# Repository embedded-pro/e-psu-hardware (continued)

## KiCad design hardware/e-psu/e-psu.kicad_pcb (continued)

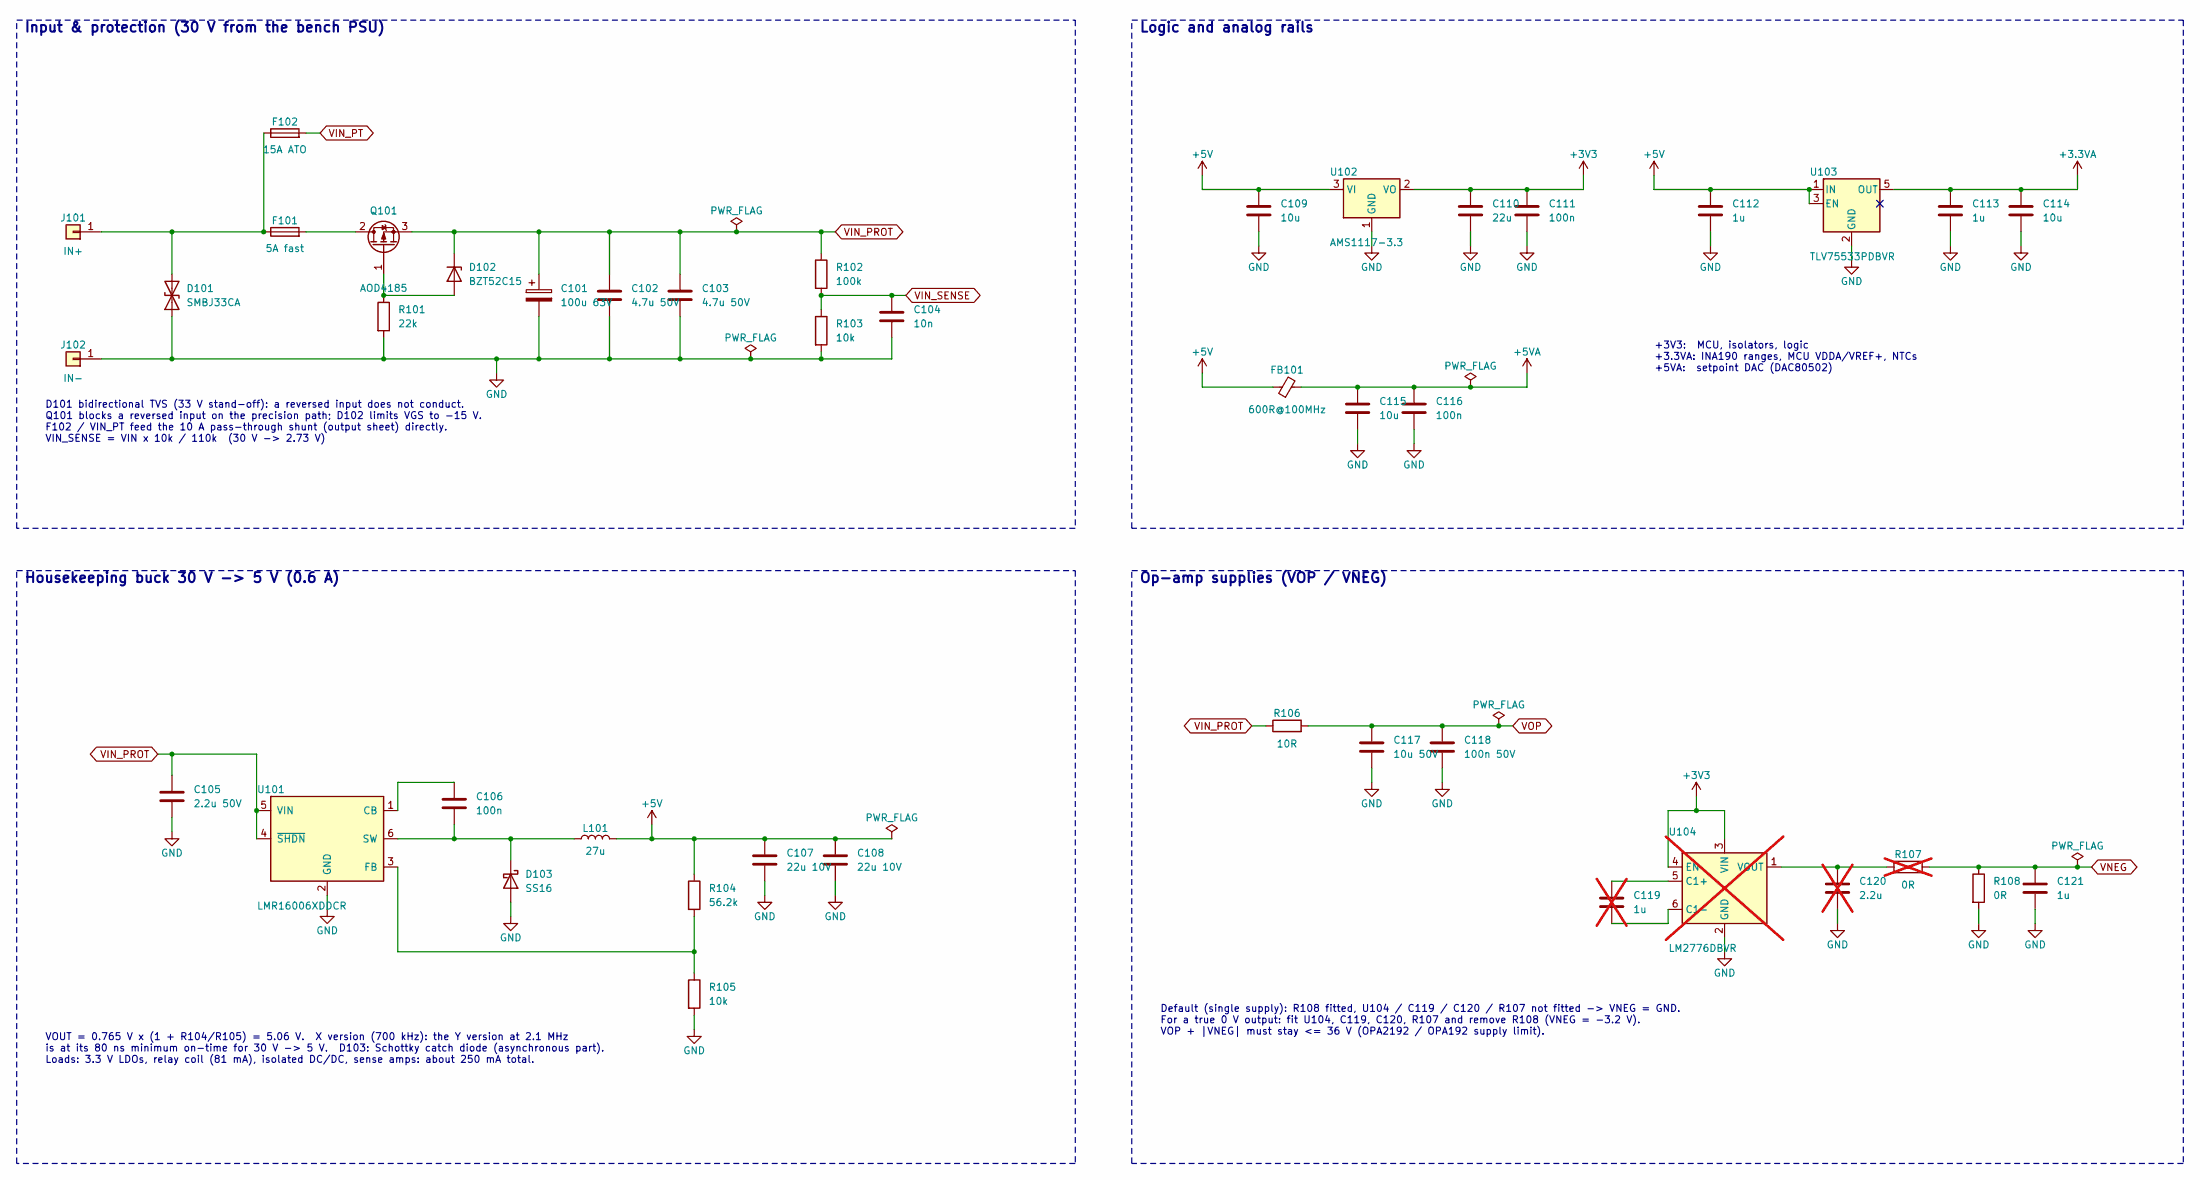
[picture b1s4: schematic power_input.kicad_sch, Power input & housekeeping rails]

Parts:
C101: 100u 63V; CP_Elec_10x10.5
C102, C103: 4.7u 50V; C_1210_3225Metric
C104: 10n; C_0603_1608Metric
C105: 2.2u 50V; C_1206_3216Metric
C106, C111, C116: 100n; C_0603_1608Metric
C107, C108: 22u 10V; C_0805_2012Metric
C109, C114, C115: 10u; C_0805_2012Metric
C110: 22u; C_1206_3216Metric
C112, C113, C121: 1u; C_0603_1608Metric
C117: 10u 50V; C_1210_3225Metric
C118: 100n 50V; C_0603_1608Metric
C119: 1u; C_0603_1608Metric; not fitted
C120: 2.2u; C_0603_1608Metric; not fitted
D101: SMBJ33CA; D_SMB; MPN SMBJ33CA (bidirectional)
D102: BZT52C15; D_SOD-123
D103: SS16; D_SMA
F101: 5A fast; Fuse_Littelfuse-NANO2-451_453; MPN Littelfuse 0451005.MRL (NANO2 5 A)
F102: 15A ATO; FuseHolder_Blade_ATO_Littelfuse_FLR_178.6165; MPN ATO blade fuse 15 A + PCB holder
FB101: 600R@100MHz; L_0805_2012Metric
J101: IN+; Banana_Cliff_FCR7350R_S16N-PC_Horizontal; MPN Cliff FCR7350R (4 mm, 16 A)
J102: IN-; Banana_Cliff_FCR7350B_S16N-PC_Horizontal; MPN Cliff FCR7350B (4 mm, 16 A)
L101: 27u; L_Sunlord_SWPA5040S; MPN 27 uH, Isat >= 1 A (e.g. Sunlord SWPA50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
Q101: AOD4185; TO-252-2; MPN AOD4185 (-40 V, 40 A, DPAK)
R101: 22k; R_0603_1608Metric
R102: 100k; R_0603_1608Metric
R103, R105: 10k; R_0603_1608Metric
R104: 56.2k; R_0603_1608Metric
R106: 10R; R_0805_2012Metric
R107: 0R; R_0603_1608Metric; not fitted
R108: 0R; R_0603_1608Metric
U101: LMR16006XDDCR; SOT-23-6; MPN TI LMR16006XDDCR (700 kHz)
U102: AMS1117-3.3; SOT-223-3_TabPin2; LCSC C6186
U103: TLV75533PDBVR; SOT-23-5; LCSC C404027
U104: LM2776DBVR; SOT-23-6; LCSC C69527; not fitted

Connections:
+3.3VA: C113.1, C114.1, U103.5 (OUT); also elsewhere on the board
+3V3: C110.1, C111.1, U102.2 (VO), U104.3 (VIN), U104.4 (EN); also elsewhere on the board
+5V: C107.1, C108.1, C109.1, C112.1, FB101.1, L101.2, R104.1, U102.3 (VI), U103.1 (IN), U103.3 (EN); also elsewhere on the board
+5VA: C115.1, C116.1, FB101.2; also elsewhere on the board
GND: C101.2, C102.2, C103.2, C104.2, C105.2, C107.2, C108.2, C109.2, C110.2, C111.2, C112.2, C113.2, C114.2, C115.2, C116.2, C117.2, C118.2, C120.2, C121.2, D101.1 (A1), D103.2 (A), J102.1, R101.2, R103.2, R105.2, R108.2, U101.2 (GND), U102.1 (GND), U103.2 (GND), U104.2 (GND); also elsewhere on the board
unnamed: D101.2 (A2), F101.1, F102.1, J101.1
unnamed: D102.2 (A), Q101.1 (G), R101.1
unnamed: C106.2, D103.1 (K), L101.1, U101.6 (SW)
unnamed: F101.2, Q101.2 (D)
unnamed: C106.1, U101.1 (CB)
unnamed: R104.2, R105.1, U101.3 (FB)
unnamed: C119.1, U104.5 (C1+)
unnamed: C119.2, U104.6 (C1-)
unnamed: C120.1, R107.1, U104.1 (VOUT)
VIN_PROT: C101.1, C102.1, C103.1, C105.1, D102.1 (K), Q101.3 (S), R102.1, R106.1, U101.4 (~SHDN), U101.5 (VIN); also elsewhere on the board
VIN_PT: F102.2; also elsewhere on the board
VIN_SENSE: C104.1, R102.2, R103.1; also elsewhere on the board
VNEG: C121.1, R107.2, R108.1; also elsewhere on the board
VOP: C117.1, C118.1, R106.2; also elsewhere on the board

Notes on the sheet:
Input & protection (30 V from the bench PSU)
D101 bidirectional TVS (33 V stand-off): a reversed input does not conduct. Q101 blocks a reversed input on the precision path; D102 limits VGS to -15 V. F102 / VIN_PT feed the 10 A pass-through shunt (output sheet) directly. VIN_SENSE = VIN x 10k / 110k (30 V -> 2.73 V)
Housekeeping buck 30 V -> 5 V (0.6 A)
VOUT = 0.765 V x (1 + R104/R105) = 5.06 V. X version (700 kHz): the Y version at 2.1 MHz is at its 80 ns minimum on-time for 30 V -> 5 V. D103: Schottky catch diode (asynchronous part). Loads: 3.3 V LDOs, relay coil (81 mA), isolated DC/DC, sense amps: about 250 mA total.
Logic and analog rails
+3V3: MCU, isolators, logic +3.3VA: INA190 ranges, MCU VDDA/VREF+, NTCs +5VA: setpoint DAC (DAC80502)
Op-amp supplies (VOP / VNEG)
Default (single supply): R108 fitted, U104 / C119 / C120 / R107 not fitted -> VNEG = GND. For a true 0 V output: fit U104, C119, C120, R107 and remove R108 (VNEG = -3.2 V). VOP + |VNEG| must stay <= 36 V (OPA2192 / OPA192 supply limit).

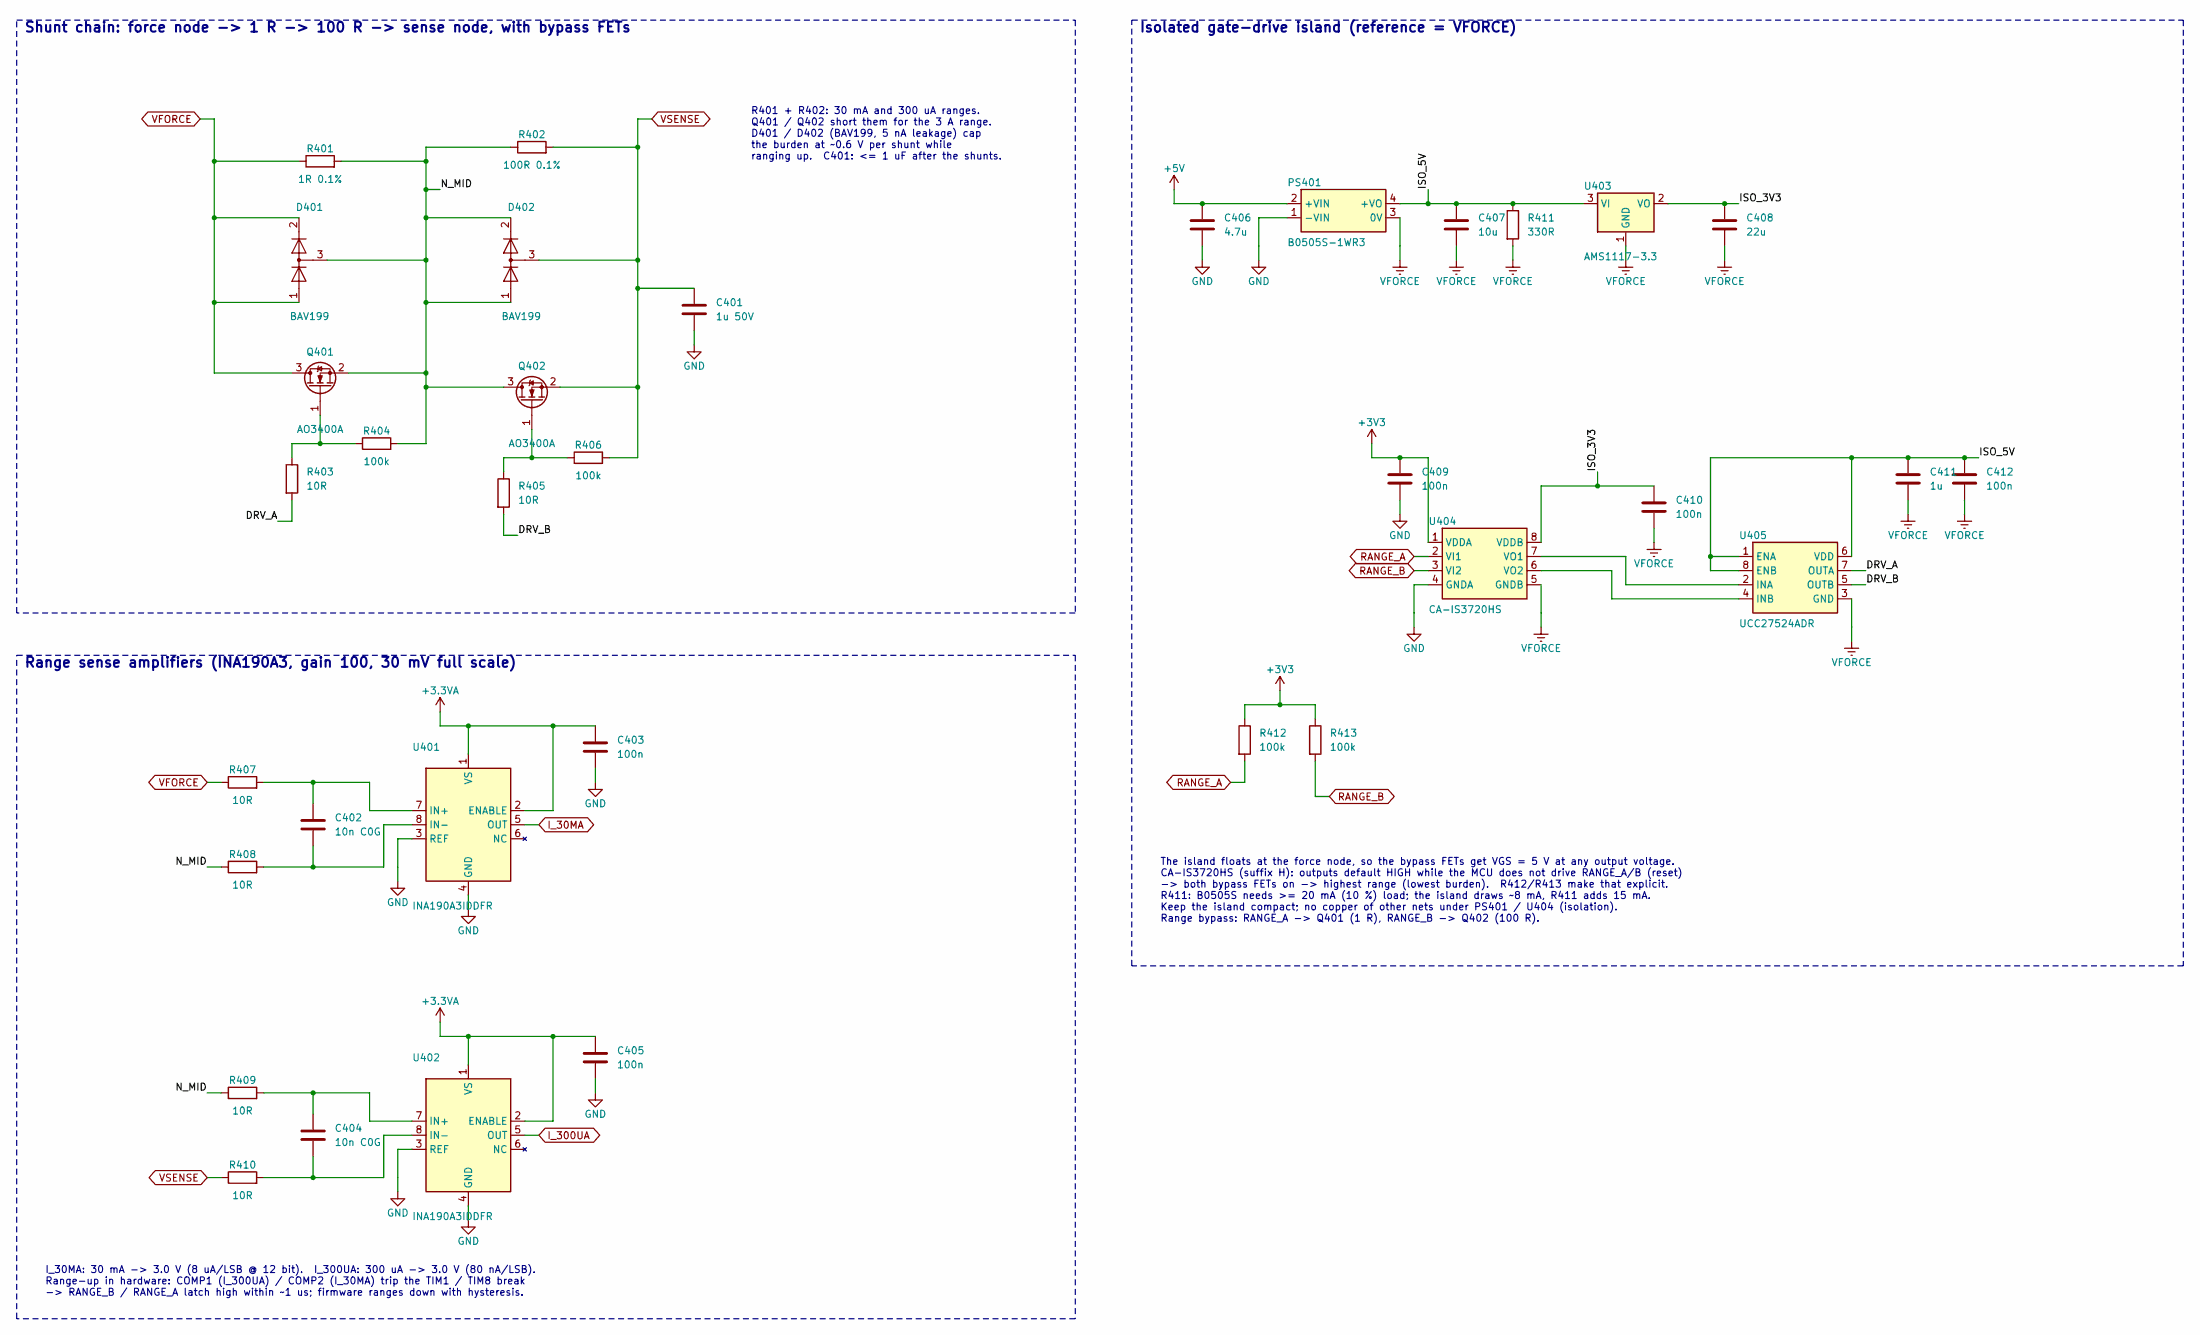
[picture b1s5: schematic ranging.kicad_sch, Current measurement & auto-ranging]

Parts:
C401: 1u 50V; C_0805_2012Metric
C402, C404: 10n C0G; C_0603_1608Metric
C403, C405, C409, C410, C412: 100n; C_0603_1608Metric
C406: 4.7u; C_0805_2012Metric
C407: 10u; C_1206_3216Metric
C408: 22u; C_1206_3216Metric
C411: 1u; C_0603_1608Metric
D401, D402: BAV199; SOT-23; LCSC C40919
PS401: B0505S-1WR3; Converter_DCDC_Murata_MEE1SxxxxSC_THT; MPN B0505S-1WR3 (1 W, SIP-4; verify pinout 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; LCSC C2992394
Q401, Q402: AO3400A; SOT-23; LCSC C20917
R401: 1R 0.1%; R_0805_2012Metric; LCSC C865286
R402: 100R 0.1%; R_0805_2012Metric; LCSC C110773
R403, R405, R407, R408, R409, R410: 10R; R_0603_1608Metric
R404, R406, R412, R413: 100k; R_0603_1608Metric
R411: 330R; R_0805_2012Metric
U401, U402: INA190A3IDDFR; SOT-23-8; LCSC C1852076
U403: AMS1117-3.3; SOT-223-3_TabPin2; LCSC C6186
U404: CA-IS3720HS; SOIC-8_3.9x4.9mm_P1.27mm; LCSC C428882
U405: UCC27524ADR; SOIC-8_3.9x4.9mm_P1.27mm; LCSC C185857

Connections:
+3.3VA: C403.1, C405.1, U401.1 (VS), U401.2 (ENABLE), U402.1 (VS), U402.2 (ENABLE); also elsewhere on the board
+3V3: C409.1, R412.1, R413.1, U404.1 (VDDA); also elsewhere on the board
+5V: C406.1, PS401.2 (+VIN); also elsewhere on the board
/Current measurement & auto-ranging/DRV_A: R403.2, U405.7 (OUTA)
/Current measurement & auto-ranging/DRV_B: R405.2, U405.5 (OUTB)
/Current measurement & auto-ranging/ISO_3V3: C408.1, C410.1, U403.2 (VO), U404.8 (VDDB)
/Current measurement & auto-ranging/ISO_5V: C407.1, C411.1, C412.1, PS401.4 (+VO), R411.1, U403.3 (VI), U405.1 (ENA), U405.6 (VDD), U405.8 (ENB)
/Current measurement & auto-ranging/N_MID: D401.3 (K), D402.1 (K), D402.2 (A), Q401.2 (S), Q402.3 (D), R401.2, R402.1, R404.2, R408.1, R409.1
GND: C401.2, C403.2, C405.2, C406.2, C409.2, PS401.1 (-VIN), U401.3 (REF), U401.4 (GND), U402.3 (REF), U402.4 (GND), U404.4 (GNDA); also elsewhere on the board
I_30MA: U401.5 (OUT); also elsewhere on the board
I_300UA: U402.5 (OUT); also elsewhere on the board
unnamed: Q401.1 (G), R403.1, R404.1
unnamed: Q402.1 (G), R405.1, R406.1
unnamed: C402.1, R407.2, U401.7 (IN+)
unnamed: C402.2, R408.2, U401.8 (IN-)
unnamed: C404.1, R409.2, U402.7 (IN+)
unnamed: C404.2, R410.2, U402.8 (IN-)
unnamed: U404.7 (VO1), U405.2 (INA)
unnamed: U404.6 (VO2), U405.4 (INB)
RANGE_A: R412.2, U404.2 (VI1); also elsewhere on the board
RANGE_B: R413.2, U404.3 (VI2); also elsewhere on the board
VFORCE: C407.2, C408.2, C410.2, C411.2, C412.2, D401.1 (K), D401.2 (A), PS401.3 (0V), Q401.3 (D), R401.1, R407.1, R411.2, U403.1 (GND), U404.5 (GNDB), U405.3 (GND); also elsewhere on the board
VSENSE: C401.1, D402.3 (K), Q402.2 (S), R402.2, R406.2, R410.1; also elsewhere on the board

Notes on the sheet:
Shunt chain: force node -> 1 R -> 100 R -> sense node, with bypass FETs
R401 + R402: 30 mA and 300 uA ranges. Q401 / Q402 short them for the 3 A range. D401 / D402 (BAV199, 5 nA leakage) cap the burden at ~0.6 V per shunt while ranging up. C401: <= 1 uF after the shunts.
Range sense amplifiers (INA190A3, gain 100, 30 mV full scale)
I_30MA: 30 mA -> 3.0 V (8 uA/LSB @ 12 bit). I_300UA: 300 uA -> 3.0 V (80 nA/LSB). Range-up in hardware: COMP1 (I_300UA) / COMP2 (I_30MA) trip the TIM1 / TIM8 break -> RANGE_B / RANGE_A latch high within ~1 us; firmware ranges down with hysteresis.
Isolated gate-drive island (reference = VFORCE)
The island floats at the force node, so the bypass FETs get VGS = 5 V at any output voltage. CA-IS3720HS (suffix H): outputs default HIGH while the MCU does not drive RANGE_A/B (reset) -> both bypass FETs on -> highest range (lowest burden). R412/R413 make that explicit. R411: B0505S needs >= 20 mA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

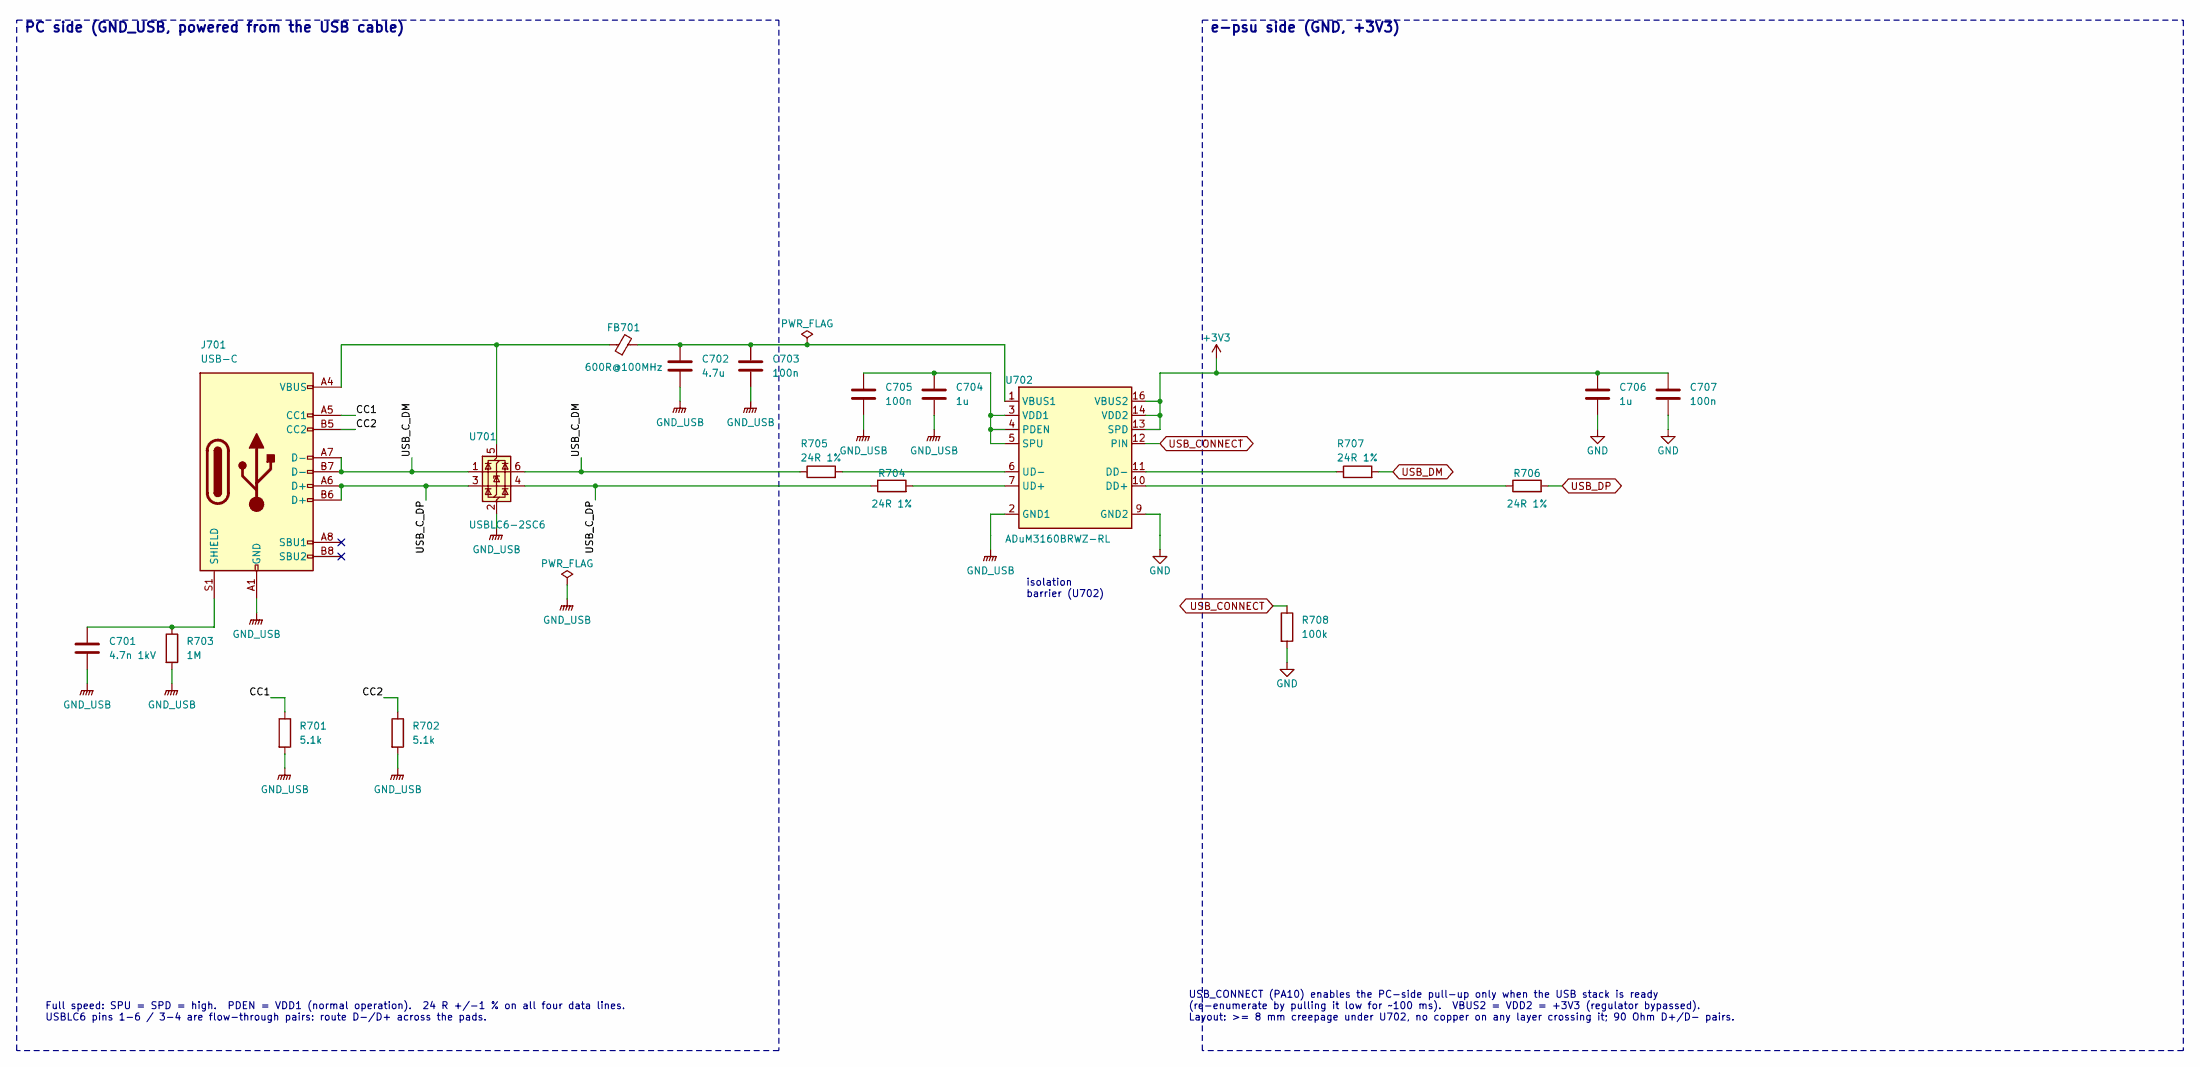
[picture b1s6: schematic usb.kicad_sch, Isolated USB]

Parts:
C701: 4.7n 1kV; C_1206_3216Metric
C702: 4.7u; C_0805_2012Metric
C703, C705, C707: 100n; C_0603_1608Metric
C704, C706: 1u; C_0603_1608Metric
FB701: 600R@100MHz; L_0805_2012Metric
J701: USB-C; USB_C_Receptacle_HRO_TYPE-C-31-M-12; LCSC C165948
R701, R702: 5.1k; R_0603_1608Metric
R703: 1M; R_0603_1608Metric
R704, R705, R706, R707: 24R 1%; R_0603_1608Metric
R708: 100k; R_0603_1608Metric
U701: USBLC6-2SC6; SOT-23-6; LCSC C7519
U702: ADuM3160BRWZ-RL; SOIC-16W_7.5x10.3mm_P1.27mm; LCSC C284149

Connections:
+3V3: C706.1, C707.1, U702.13 (SPD), U702.14 (VDD2), U702.16 (VBUS2); also elsewhere on the board
/Isolated USB/CC1: J701.A5 (CC1), R701.1
/Isolated USB/CC2: J701.B5 (CC2), R702.1
/Isolated USB/USB_C_DM: J701.A7 (D-), J701.B7 (D-), R705.1, U701.1 (I/O1), U701.6 (I/O1)
/Isolated USB/USB_C_DP: J701.A6 (D+), J701.B6 (D+), R704.1, U701.3 (I/O2), U701.4 (I/O2)
GND: C706.2, C707.2, R708.2, U702.9 (GND2), U702.15 (GND2); also elsewhere on the board
GND_USB: C701.2, C702.2, C703.2, C704.2, C705.2, J701.A1 (GND), J701.A12 (GND), J701.B1 (GND), J701.B12 (GND), R701.2, R702.2, R703.2, U701.2 (GND), U702.2 (GND1), U702.8 (GND1)
unnamed: C701.1, J701.S1 (SHIELD), R703.1
unnamed: FB701.1, J701.A4 (VBUS), J701.A9 (VBUS), J701.B4 (VBUS), J701.B9 (VBUS), U701.5 (VBUS)
unnamed: R706.1, U702.10 (DD+)
unnamed: R707.1, U702.11 (DD-)
unnamed: C704.1, C705.1, U702.3 (VDD1), U702.4 (PDEN), U702.5 (SPU)
unnamed: R704.2, U702.7 (UD+)
unnamed: R705.2, U702.6 (UD-)
unnamed: C702.1, C703.1, FB701.2, U702.1 (VBUS1)
USB_CONNECT: R708.1, U702.12 (PIN); also elsewhere on the board
USB_DM: R707.2; also elsewhere on the board
USB_DP: R706.2; also elsewhere on the board

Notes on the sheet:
PC side (GND_USB, powered from the USB cable)
e-psu side (GND, +3V3)
isolation barrier (U702)
Full speed: SPU = SPD = high. PDEN = VDD1 (normal operation). 24 R +/-1 % on all four data lines. USBLC6 pins 1-6 / 3-4 are flow-through pairs: route D-/D+ across the pads.
USB_CONNECT (PA10) enables the PC-side pull-up only when the USB stack is ready (re-enumerate by pulling it low for ~100 ms). VBUS2 = VDD2 = +3V3 (regulator bypassed). Layout: >= 8 mm creepage under U702, no copper on any layer crossing it; 90 Ohm D+/D- pairs.

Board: 4 copper layers, 244 parts (0 on the bottom side), 131 nets, no tracks yet.

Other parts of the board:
C501, C503: 100n; C_0603_1608Metric
C502: 100n 50V; C_0603_1608Metric
D501: 1N4148W; D_SOD-123
D502: SMBJ33CA; D_SMB
J501: OUT+; Banana_Cliff_FCR7350R_S16N-PC_Horizontal
J502: OUT-; Banana_Cliff_FCR7350B_S16N-PC_Horizontal
K501: HF115F/005-1ZS3; Relay_SPDT_Schrack-RT1-16A-FormC_RM5mm
Q501, Q504, Q505: AO3400A; SOT-23
Q502, Q503: NTMFS5C430N; ONSemi_SO-8FL_488AA
R501: 2m 1% 3W; R_2512_6332Metric
R502, R506: 100R; R_0603_1608Metric
R503, R507: 100k; R_0603_1608Metric
R504: 1M; R_0603_1608Metric
R505: 82R; R_0603_1608Metric
R508: 1M 0.1%; R_0603_1608Metric
R509: 110k 0.1%; R_0603_1608Metric
U501: INA281A3IDBVR; SOT-23-5
U502: VOM1271T; SO-4_4.4x3.6mm_P2.54mm

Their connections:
+3V3: R505.1; also elsewhere on the board
+5V: C501.1, D501.1, K501.A1, U501.5; also elsewhere on the board
/Pass-through & output switch/OUT_P: C502.1, D502.2, J501.1, Q503.5, R508.1
/Pass-through & output switch/SRC_COM: Q502.1, Q502.2, Q502.3, Q503.1, Q503.2, Q503.3, R504.2, U502.3
/Pass-through & output switch/SW_IN: K501.11, Q502.5
GND: C501.2, C502.2, C503.2, D502.1, J502.1, Q501.2, Q504.2, Q505.2, R503.2, R507.2, R509.2, U501.2; also elsewhere on the board
I_PT: U501.1; also elsewhere on the board
unnamed: D501.2, K501.A2, Q501.3
unnamed: Q501.1, R502.2, R503.1
unnamed: Q502.4, Q503.4, R504.1, U502.4
unnamed: Q504.3, U502.2
unnamed: Q504.1, R506.2, R507.1
unnamed: Q505.3, R505.2, U502.1
unnamed: K501.14, R501.2, U501.4
OCP_TRIP: Q505.1; also elsewhere on the board
OUT_EN: R506.1; also elsewhere on the board
RELAY_PT: R502.1; also elsewhere on the board
VIN_PT: R501.1, U501.3; also elsewhere on the board
VOUT_TERM: C503.1, R508.2, R509.1; also elsewhere on the board
VSENSE: K501.12; also elsewhere on the board

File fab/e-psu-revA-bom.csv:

Comment,Designator,Footprint,LCSC Part #,MPN,Qty
100u 63V,C101,CP_Elec_10x10.5,,,1
4.7u 50V,"C102,C103,C201,C202",C_1210_3225Metric,,,4
10n,"C104,C214,C319,C321,C607",C_0603_1608Metric,,,5
2.2u 50V,C105,C_1206_3216Metric,,,1
100n,"C106,C111,C116,C301,C303,C308,C309,C311,C316,C403,C405,C409,C410,C412,C501,C503,C601,C602,C603,C604,C609,C610,C613,C614,C615,C703,C705,C707",C_0603_1608Metric,,,28
22u 10V,"C107,C108",C_0805_2012Metric,,,2
10u,"C109,C114,C115",C_0805_2012Metric,,,3
22u,"C110,C408",C_1206_3216Metric,,,2
1u,"C112,C113,C121,C206,C310,C411,C606,C608,C704,C706",C_0603_1608Metric,,,10
10u 50V,"C117,C207,C208,C209,C210,C313",C_1210_3225Metric,,,6
100n 50V,"C118,C203,C302,C314,C320,C502",C_0603_1608Metric,,,6
470n,C204,C_0603_1608Metric,,,1
2.2u 10V,C205,C_0603_1608Metric,,,1
47u 50V,C211,CP_Elec_8x10,,,1
5.6n C0G,C304,C_0603_1608Metric,,,1
1n C0G,C306,C_0603_1608Metric,,,1
1.5n C0G,C307,C_0603_1608Metric,,,1
220n,C322,C_0603_1608Metric,,,1
1u 50V,C401,C_0805_2012Metric,,,1
10n C0G,"C402,C404",C_0603_1608Metric,,,2
4.7u,"C406,C605,C702",C_0805_2012Metric,,,3
10u,C407,C_1206_3216Metric,,,1
27p C0G,"C611,C612",C_0603_1608Metric,,,2
4.7n 1kV,C701,C_1206_3216Metric,,,1
SMBJ33CA,"D101,D502",D_SMB,,SMBJ33CA (bidirectional),2
BZT52C15,"D102,D303,D304",D_SOD-123,,,3
SS16,D103,D_SMA,,,1
1N4148W,"D301,D302,D501",D_SOD-123,,,3
BAV199,"D401,D402",SOT-23,C40919,,2
green CV,D601,LED_0603_1608Metric,,,1
red CC,D602,LED_0603_1608Metric,,,1
yellow OUT,D603,LED_0603_1608Metric,,,1
blue PASS,D604,LED_0603_1608Metric,,,1
5A fast,F101,Fuse_Littelfuse-NANO2-451_453,,Littelfuse 0451005.MRL (NANO2 5 A),1
15A ATO,F102,FuseHolder_Blade_ATO_Littelfuse_FLR_178.6165,,ATO blade fuse 15 A + PCB holder,1
600R@100MHz,"FB101,FB701",L_0805_2012Metric,,,2
IN+,J101,Banana_Cliff_FCR7350R_S16N-PC_Horizontal,,"Cliff FCR7350R (4 mm, 16 A)",1
IN-,J102,Banana_Cliff_FCR7350B_S16N-PC_Horizontal,,"Cliff FCR7350B (4 mm, 16 A)",1
OUT+,J501,Banana_Cliff_FCR7350R_S16N-PC_Horizontal,,Cliff FCR7350R,1
OUT-,J502,Banana_Cliff_FCR7350B_S16N-PC_Horizontal,,Cliff FCR7350B,1
SWD,J601,PinHeader_2x05_P1.27mm_Vertical_SMD,C5160761,Cortex debug 2x5 1.27 mm,1
USB-C,J701,USB_C_Receptacle_HRO_TYPE-C-31-M-12,C165948,,1
HF115F/005-1ZS3,K501,Relay_SPDT_Schrack-RT1-16A-FormC_RM5mm,C9225,Hongfa HF115F/005-1ZS3 (verify pin map vs RT1 footprint),1
27u,L101,L_Sunlord_SWPA5040S,,"27 uH, Isat >= 1 A (e.g. Sunlord SWPA5040S270MT)",1
15u,L201,L_Wuerth_HCI-1350,C20415554,FANGCHENG FCH1365-150M (Isat 12 A),1
B0505S-1WR3,PS401,Converter_DCDC_Murata_MEE1SxxxxSC_THT,C2992394,"B0505S-1WR3 (1 W, SIP-4; verify pinout vs maker drawing)",1
AOD4185,Q101,TO-252-2,,"AOD4185 (-40 V, 40 A, DPAK)",1
IRFP260N,Q301,TO-247-3_Vertical,C2678,Infineon IRFP260NPBF on heatsink (or a linear-mode FET with DC SOA),1
2N7002,"Q302,Q303",SOT-23,,,2
BCX56-16,Q304,SOT-89-3,,"BCX56-16 (SOT-89, 1 W): ~0.25 W at 24 V / 10 mA",1
AO3400A,"Q401,Q402,Q501,Q504,Q505",SOT-23,C20917,,5
NTMFS5C430N,"Q502,Q503",ONSemi_SO-8FL_488AA,C604436,,2
22k,"R101,R312",R_0603_1608Metric,,,2
100k,"R102,R201,R202,R204,R205,R206,R308,R317,R404,R406,R412,R413,R503,R507,R708",R_0603_1608Metric,,,15
10k,"R103,R105,R207,R306,R309,R316,R321,R324,R601,R602,R607",R_0603_1608Metric,,,11
56.2k,R104,R_0603_1608Metric,,,1
10R,R106,R_0805_2012Metric,,,1
0R,"R108,R314",R_0603_1608Metric,,,2
3.16k 0.1%,R203,R_0603_1608Metric,,,1
15m 1% 3W,R301,R_2512_6332Metric,C459682,,1
90.9k 0.1%,"R303,R325",R_0603_1608Metric,,,2
10k 0.1%,"R304,R326",R_0603_1608Metric,,,2
3.9k,R305,R_0603_1608Metric,,,1
1k,"R307,R310,R311,R322,R603,R604,R605",R_0603_1608Metric,,,7
100R,"R313,R318,R502,R506",R_0603_1608Metric,,,4
68R,R319,R_0805_2012Metric,,,1
15k,R320,R_0603_1608Metric,,,1
8.2k,R327,R_0603_1608Metric,,,1
1R 0.1%,R401,R_0805_2012Metric,C865286,,1
100R 0.1%,R402,R_0805_2012Metric,C110773,,1
10R,"R403,R405,R407,R408,R409,R410",R_0603_1608Metric,,,6
330R,R411,R_0805_2012Metric,,,1
2m 1% 3W,R501,R_2512_6332Metric,C459679,,1
1M,"R504,R703",R_0603_1608Metric,,,2
82R,R505,R_0603_1608Metric,,,1
1M 0.1%,R508,R_0603_1608Metric,,,1
110k 0.1%,R509,R_0603_1608Metric,,,1
470R,R606,R_0603_1608Metric,,,1
5.1k,"R701,R702",R_0603_1608Metric,,,2
24R 1%,"R704,R705,R706,R707",R_0603_1608Metric,,,4
OUTPUT,SW601,SW_SPST_PTS645,,,1
10k B3380,TH301,R_0603_1608Metric,C13564,"Murata NCP18XH103F03RB, on the heatsink side of Q301",1
10k B3380,TH601,R_0603_1608Metric,C13564,,1
LMR16006XDDCR,U101,SOT-23-6,,TI LMR16006XDDCR (700 kHz),1
AMS1117-3.3,"U102,U403",SOT-223-3_TabPin2,C6186,,2
TLV75533PDBVR,U103,SOT-23-5,C404027,,1
LM76003RNPR,U201,TI_RNP0030B_WQFN-30,C470958,TI LM76003RNPR,1
INA293A2IDBVR,U301,SOT-23-5,C1855792,,1
OPA2192IDR,U302,SOIC-8_3.9x4.9mm_P1.27mm,C110074,,1
OPA192IDR,U303,SOIC-8_3.9x4.9mm_P1.27mm,C2861286,,1
DAC80502DRXT,U304,Texas_DRX_WSON-10_2.5x2.5mm_P0.5mm,C2861168,,1
INA190A3IDDFR,"U401,U402",SOT-23-8,C1852076,,2
CA-IS3720HS,U404,SOIC-8_3.9x4.9mm_P1.27mm,C428882,,1
UCC27524ADR,U405,SOIC-8_3.9x4.9mm_P1.27mm,C185857,,1
INA281A3IDBVR,U501,SOT-23-5,C1517407,,1
VOM1271T,U502,SO-4_4.4x3.6mm_P2.54mm,C146286,"Vishay VOM1271T (check output polarity: pin 4 = +, pin 3 = -)",1
STM32G474RET6,U601,LQFP-64_10x10mm_P0.5mm,C521608,"STM32G474RET6 (fallback STM32G431RBT6, C431633)",1
USBLC6-2SC6,U701,SOT-23-6,C7519,,1
ADuM3160BRWZ-RL,U702,SOIC-16W_7.5x10.3mm_P1.27mm,C284149,,1
8MHz,Y601,Crystal_SMD_HC49-SD,C12674,,1

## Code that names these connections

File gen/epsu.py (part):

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              fp="Capacitor_SMD:CP_Elec_10x10.5"),
            C(sh, "C102", "4.7u 50V", 121.92, 69.85, "VIN_PROT", fp=C1210),
            C(sh, "C103", "4.7u 50V", 134.62, 69.85, "VIN_PROT", fp=C1210)]
    fvp = sh.flag("VIN_PROT", (144.78, 58.42), label=False)
    fg = sh.flag("GND", (147.32, 81.28), label=False)
    r102 = R(sh, "R102", "100k", 160.02, 66.04, "VIN_PROT", "VIN_SENSE")
    r103 = R(sh, "R103", "10k", 160.02, 76.2, "VIN_SENSE", "GND")
    c104 = C(sh, "C104", "10n", 172.72, 73.66, "VIN_SENSE")
    sh.rail("VIN_RAW", 58.42, [j1["1"], tvs["2"], f1["1"], f2["1"]])
    sh.rail("VIN_PROT", 58.42, [q["S"], d102["1"]] + [c["1"] for c in caps] + [fvp["1"], r102["1"]], label="right")
    sh.rail("PFET_G", 69.85, [q["G"], r101["1"], d102["2"]])
    sh.rail("VIN_SENSE", 69.85, [r102["2"], r103["1"], c104["1"]], label="right")
    sh.rail("GND", 81.28, [j2["1"], tvs["1"], r101["2"]] + [c["2"] for c in caps] + [fg["1"], r103["2"], c104["2"]],
            tap=(101.6, (0, 1)))
    note(sh, 20.32, 96.52, [
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    c107 = C(sh, "C107", "22u 10V", 149.86, 171.45, "+5V", fp=C0805)
    c108 = C(sh, "C108", "22u 10V", 162.56, 171.45, "+5V", fp=C0805)
    f5 = sh.flag("+5V", (172.72, 167.64), label=False)
    sh.rail("VIN_PROT", 152.4, [c105["1"], u["5"]], label="left")
    sh.rail("CB_5V", 157.48, [u["1"], c106["1"]])
    sh.rail("SW_5V", 167.64, [u["6"], c106["2"], d103["1"], l1["1"]])
    sh.rail("+5V", 167.64, [l1["2"], r104["1"], c107["1"], c108["1"], f5["1"]], tap=(129.54, (0, -1)))
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    r106 = R(sh, "R106", "10R", 243.84, 147.32, "VIN_PROT", "VOP", rot=90, fp=R0805)
    c117 = C(sh, "C117", "10u 50V", 259.08, 151.13, "VOP", fp=C1210)
    c118 = C(sh, "C118", "100n 50V", 271.78, 151.13, "VOP")
    fvop = sh.flag("VOP", (281.94, 147.32), label=False)
    sh.rail("VOP", 147.32, [r106["2"], c117["1"], c118["1"], fvop["1"]], label="right")
    u4 = sh.part("Regulator_SwitchedCapacitor:LM2776", "U104", "LM2776DBVR", (322.58, 175.26), fp=SOT23_6,
                 lcsc="C69527", dnp=True)
    sh.net(u4["2"], "GND")
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    r107 = sh.part("Device:R", "R107", "0R", (355.6, 172.72), 90, fp=R0603, dnp=True)
    r108 = R(sh, "R108", "0R", 368.3, 176.53, "VNEG", "GND")
    c121 = C(sh, "C121", "1u", 378.46, 176.53, "VNEG")
    fvn = sh.flag("VNEG", (386.08, 172.72), label=False)
    sh.rail("VNEG_CP", 172.72, [u4["1"], c120["1"], r107["1"]])
    sh.rail("VNEG", 172.72, [r107["2"], r108["1"], c121["1"], fvn["1"]], label="right")
    note(sh, 220.98, 203.2, [
        "Default (single supply): R108 fitted, U104 / C119 / C120 / R107 not fitted -> VNEG = GND.",
        "For a true 0 V output: fit U104, C119, C120, R107 and remove R108 (VNEG = -3.2 V).",
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    cin = [C(sh, "C203", "100n 50V", 63.5, 77.47, "VIN_PROT"),
           C(sh, "C201", "4.7u 50V", 78.74, 77.47, "VIN_PROT", fp=C1210),
           C(sh, "C202", "4.7u 50V", 93.98, 77.47, "VIN_PROT", fp=C1210)]
    sh.rail("VIN_PROT", 73.66, [c["1"] for c in cin] + [u["20"]], label="left")
    r204 = R(sh, "R204", "100k", 86.36, 95.25, "BUCK_EN", "GND")
    sh.rail("BUCK_EN", 91.44, [u["18"], r204["1"]], label="left")
    c206 = C(sh, "C206", "1u", 93.98, 105.41, "+3V3")
    sh.link(u["17"], u["9"], "+3V3")
    sh.rail("+3V3", 101.6, [u["9"], c206["1"]], tap=(104.14, (0, -1)))
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                 lcsc="C20415554", mpn="FANGCHENG FCH1365-150M (Isat 12 A)")
    sh.rail("SW_BUCK", 73.66, [u["1"], c204["1"], l2["1"]], tap=(157.48, (0, -1)))
    r205 = R(sh, "R205", "100k", 160.02, 90.17, "+3V3", "BUCK_PG")
    sh.rail("BUCK_PG", 93.98, [u["16"], r205["2"]], label="right")
    c205 = C(sh, "C205", "2.2u 10V", 149.86, 107.95, "VCC_BUCK")
    sh.link(u["8"], c205["1"], "VCC_BUCK")
    # output and feedback
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    r206 = R(sh, "R206", "100k", 325.12, 77.47, "VPRE", "VPRE_SENSE")
    r207 = R(sh, "R207", "10k", 325.12, 88.9, "VPRE_SENSE", "GND")
    c214 = C(sh, "C214", "10n", 337.82, 87.63, "VPRE_SENSE")
    sh.rail("VPRE", 73.66, [l2["2"]] + [c["1"] for c in cout] + [r201["1"], c213["1"], r206["1"]], label="right")
    sh.rail("FB_BUCK", 99.06, [u["12"], r201["2"], c213["2"], r202["1"], r203["1"]])
    sh.rail("VPRE_SENSE", 83.82, [r206["2"], r207["1"], c214["1"]], label="right")
    note(sh, 20.32, 45.72, [
        "VPRE = VFB (1 + R201/R202) + (VFB - V_BUCK_DAC) R201/R203,  VFB = 1.006 V",
        "BUCK_DAC 0.2 V -> 27.5 V;  1.0 V -> 2.0 V;  ~25 mV per G474 DAC step.",
        "MCU in reset: PA4 is high-impedance -> no injection -> VPRE = 2.0 V (safe default).",
        "Firmware rule: VPRE = measured VOUT + 1.5 V; raise VPRE before VOUT, lower VOUT before VPRE."])
    note(sh, 220.98, 129.54, [
        "RT open = 500 kHz.  SYNC/MODE high = forced PWM (VPRE can be pulled down).",
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    c216 = sh.part("Device:C", "C216", "100n 50V", (119.38, y + 3.81), fp=C0603, dnp=True)
    d203 = sh.part("Device:D_Zener", "D203", "BZT52C10", (137.16, y + 3.81), 270, fp=SOD123, dnp=True)
    sh.rail("PUMP_A", y, [c215["2"], d201["1"], d202["2"]])
    sh.rail("V_GATE", y, [d202["1"], c216["1"], d203["1"]], label="right", ext=7.62)
    sh.rail("VIN_PROT", y + 12.7, [d201["2"], c216["2"], d203["2"]], label="left", ext=5.08)
    note(sh, 170.18, 177.8, ["Fit to raise the maximum output from ~24 V to ~27 V:",
                             "fit R208, C215, D201-D203, C216 and R315 (linear sheet),",
                             "remove R314."])
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    q = sh.part("Transistor_FET:IRF540N", "Q301", "IRFP260N", (60.96, 66.04), fp="Package_TO_SOT_THT:TO-247-3_Vertical",
                lcsc="C2678", mpn="Infineon IRFP260NPBF on heatsink (or a linear-mode FET with DC SOA)")
    q.fpos = (5.08, -1.27, "left")
    sh.rail("VPRE", 50.8, [q["2"]], label="left", ext=7.62)
    r313 = R(sh, "R313", "100R", 40.64, 66.04, "GATE_DRV", "GATE", rot=90)
    d303 = D(sh, "Device:D_Zener", "D303", "BZT52C15", 50.8, 72.39, "GATE", "ZCLAMP", rot=270)
    d304 = D(sh, "Device:D_Zener", "D304", "BZT52C15", 50.8, 83.82, "VSRC", "ZCLAMP", rot=90)
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    r318 = R(sh, "R318", "100R", 109.22, 100.33, "VFORCE", "BLD_C")
    c313 = C(sh, "C313", "10u 50V", 127.0, 95.25, "VFORCE", fp=C1210)
    c314 = C(sh, "C314", "100n 50V", 139.7, 95.25, "VFORCE")
    sh.rail("VFORCE", 91.44, [r301["2"], r318["1"], c313["1"], c314["1"]], label="right", ext=5.08)
    bj = sh.part("Transistor_BJT:BCX56", "Q304", "BCX56-16", (106.68, 111.76), fp="Package_TO_SOT_SMD:SOT-89-3",
                 mpn="BCX56-16 (SOT-89, 1 W): ~0.25 W at 24 V / 10 mA")
    sh.net(bj["C"], "BLD_C"); sh.net(bj["E"], "BLD_E")
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                 mpn="Murata NCP18XH103F03RB, on the heatsink side of Q301")
    sh.net(th["2"], "GND")
    c316 = C(sh, "C316", "100n", 182.88, 113.03, "NTC_PASS")
    sh.rail("NTC_PASS", 109.22, [r324["2"], th["1"], c316["1"]], label="right")
    note(sh, 20.32, 38.1, [
        "I_3A = 15 mOhm x 50 = 0.75 V/A (3.33 A full scale).  D303/D304: |VGS| <= 15.7 V.",
        "Q304: 10 mA bleeder at the force node keeps the loop in control at no load",
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    sh.rail("VGATE_SUP", 152.4, [r314["2"], r315["2"], r312["1"]])
    q2 = Q3(sh, "Transistor_FET:2N7002", "Q302", "2N7002", 55.88, 185.42, "GATE_HOLD", "GATE_DRV", "GND")
    r316 = R(sh, "R316", "10k", 45.72, 181.61, "+3V3", "GATE_HOLD")
    sh.rail("GATE_HOLD", 185.42, [q2["G"], r316["2"]], label="left")
    q3 = Q3(sh, "Transistor_FET:2N7002", "Q303", "2N7002", 96.52, 185.42, "OCP_TRIP", "GATE_DRV", "GND")
    r317 = R(sh, "R317", "100k", 86.36, 189.23, "OCP_TRIP", "GND")
    sh.rail("OCP_TRIP", 185.42, [q3["G"], r317["1"]], label="left")
    for qq in (q2, q3):
        qq.fpos = (5.08, -1.27, "left")
    d301 = D(sh, "Diode:1N4148W", "D301", "1N4148W", 124.46, 180.34, "CV_OUT", "GATE_DRV", rot=180)
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    r310 = R(sh, "R310", "1k", 107.95, 248.92, "DAC_A", "DAC_CV_F", rot=90)
    c308 = C(sh, "C308", "100n", 124.46, 252.73, "DAC_CV_F")
    sh.link(dac["2"], r310["1"], "DAC_A")
    sh.rail("DAC_CV_F", 248.92, [r310["2"], c308["1"]], label="right")
    r311 = R(sh, "R311", "1k", 104.14, 259.08, "DAC_B", "DAC_CC_F")
    sh.link(dac["9"], r311["1"], "DAC_B", via="h")
    c309 = C(sh, "C309", "100n", 116.84, 270.51, "DAC_CC_F")
    sh.rail("DAC_CC_F", 266.7, [r311["2"], c309["1"]], label="right")
    note(sh, 160.02, 241.3, ["RSTSEL = GND: zero scale at", "power-up (0 V / 0 A).",
                             "SPI2C = GND: SPI mode.", "Firmware writes GAIN = 0x0103",
                             "(REF-DIV=1, gain 2) -> 2.5 V FS.", "CV: 0.4 mV/LSB, CC: 51 uA/LSB"])
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    r322 = R(sh, "R322", "1k", 248.92, 60.96, "VSENSE", "SNS_IN", rot=90)
    sh.net(buf["3"], "SNS_IN")
    c320 = C(sh, "C320", "100n 50V", 271.78, 49.53, "VOP")
    sh.rail("VOP", 45.72, [buf["7"], c320["1"]], label="left")
    sh.rail("VNEG", 76.2, [buf["4"]], label="right")
    sh.path("VS_BUF", [buf["2"], (254.0, 66.04), (254.0, 81.28), (281.94, 81.28)])
    r325 = R(sh, "R325", "90.9k 0.1%", 292.1, 67.31, "VS_BUF", "VOUT_ADC")
    r326 = R(sh, "R326", "10k 0.1%", 292.1, 82.55, "VOUT_ADC", "GND")
    c321 = C(sh, "C321", "10n", 304.8, 78.74, "VOUT_ADC")
    sh.rail("VOUT_ADC", 74.93, [r325["2"], r326["1"], c321["1"]], label="right")
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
